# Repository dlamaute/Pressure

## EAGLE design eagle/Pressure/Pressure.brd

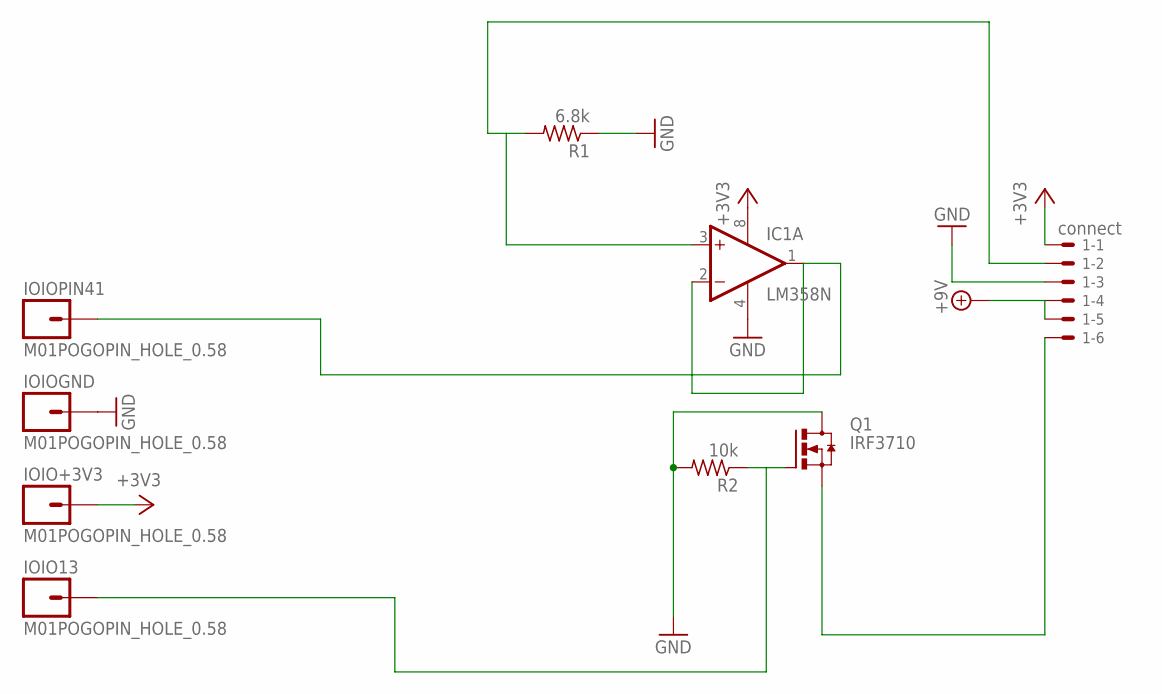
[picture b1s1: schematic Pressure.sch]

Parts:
1: connect; 70543-06
IC1: LM358N; DIL08
IOIO13: M01POGOPIN_HOLE_0.58; 1X01_POGOPIN_HOLE_0.58
IOIO+3V3: M01POGOPIN_HOLE_0.58; 1X01_POGOPIN_HOLE_0.58
IOIOGND: M01POGOPIN_HOLE_0.58; 1X01_POGOPIN_HOLE_0.58
IOIOPIN41: M01POGOPIN_HOLE_0.58; 1X01_POGOPIN_HOLE_0.58
Q1: IRF3710; TO-220AB
R1: 6.8k; 0204/7
R2: 10k; 0204/7

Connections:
+3V3: 1.1, IC1.8 (V+), IOIO+3V3.1
+9V: 1.4, 1.5
GND: 1.3, IC1.4 (V-), IOIOGND.1, Q1.A2 (D), R1.1, R2.2
unnamed: 1.2, IC1.3 (+IN), R1.2
unnamed: IC1.1 (OUT), IC1.2 (-IN), IOIOPIN41.1
unnamed: 1.6, Q1.C (S)
unnamed: IOIO13.1, Q1.A1 (G), R2.1

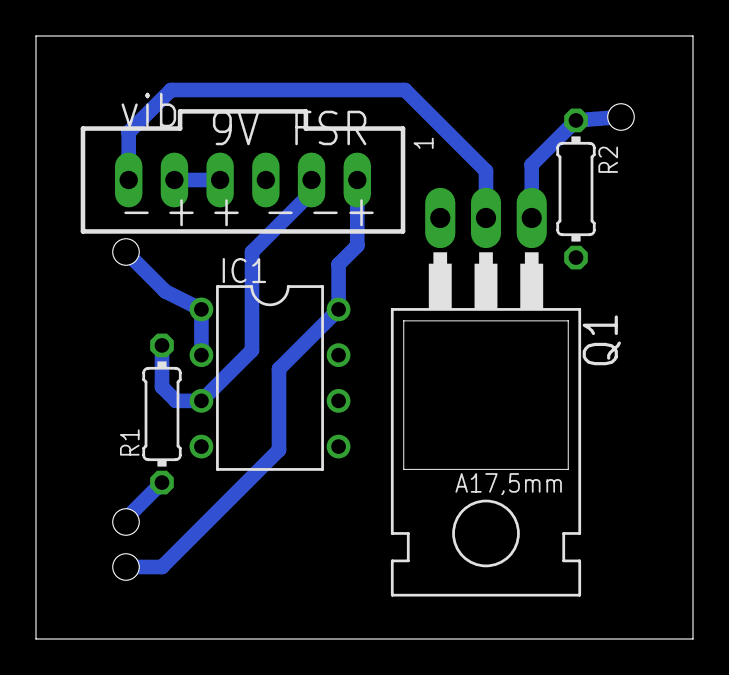
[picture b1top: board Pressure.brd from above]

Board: 2 copper layers, 36.5 x 33.5 mm, 9 parts (0 on the bottom side), 7 nets.

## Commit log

2014-01-31 UNSTABLE: The rate is not changing with voltage.
2014-02-04 PROGRESS: unstable
    Trying IOIO threading
2014-02-05 MORE or LESS:
    The LED reacts to the pressure sensor while each are on different
    threads. But I'm not seeing the Log messages from either thread.
2014-02-06 STABLE :) added:
    UI Numeric feedback
2014-02-07 UN-STABLE
    The decimial point is not fixed
2014-02-12 STABLE
    need to fix the variation of the value.
2014-02-13 STABLE
    Tweaked the code to work with the OpAmp
2014-02-24 CHANGED: To OpenDrain or not to OpenDrain
    The new MOSFETs seem to require more than 3.3
2014-03-10 NON-STABLE
    If the Log.i are on it won't work.
2014-03-11 CHANGED MANIFEST
    Added USB library for when Bluetooth doesn't work.
2014-04-09 ADDED: Sensitivity buttons and...
    better rate control.
    Transducer gets really hot
2014-04-15 Using map function
2014-04-18 Coomit from Samsung
2014-04-22 Added Eagle Files
2014-05-14 New version of boards named 'orig board' (my bad)

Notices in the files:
parts and their libraries:
SparkFun-Connectors: Licensing: CC v3.0 Share-Alike You are welcome to use this library for commercial purposes.
